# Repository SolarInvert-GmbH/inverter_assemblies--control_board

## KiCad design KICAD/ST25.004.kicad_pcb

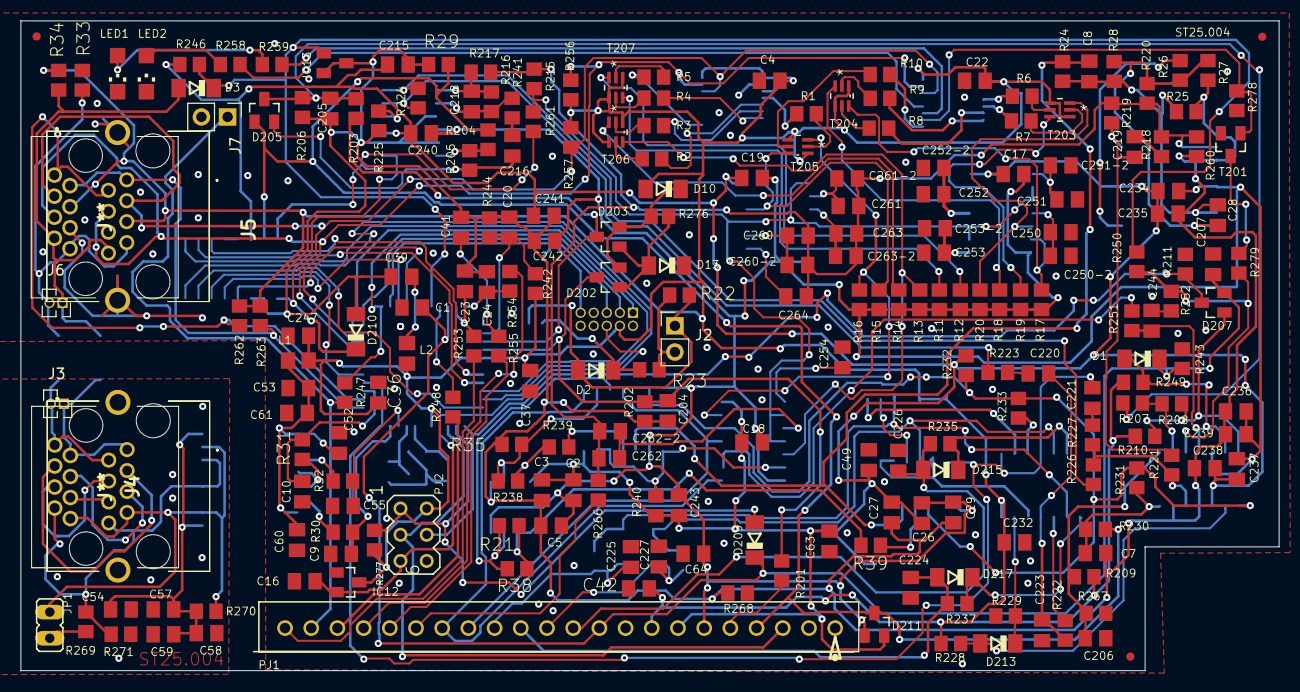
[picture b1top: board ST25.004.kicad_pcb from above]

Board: 2 copper layers, 122.0 x 63.0 mm, 257 parts (0 on the bottom side), 169 nets.

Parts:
C1, C52, C205, C207, C244, C252: 10nF; C0805K
C2, C3, C4, C5, C17, C18, C19, C20, C22, C23, C24, C26, C27, C29, C37, C39, C41, C49, C54, C57, C58, C60, C61, C63, C64, C206, C215, C232, C234, C235, C236, C237, C238, C239, C240, C241, C242, C243, C247: 100nF; C0805K
C7, C224, C225, C226, C227: 100pF; C0805K
C8, C28: n.b.; C0805K
C9, C10, C55, C245, C246: 12pF; C0805K
C16, C36, C204, C219, C223, C250-2: 1nF; C0805K
C42, C53, C59, C216, C220, C221: 10uF/16V; C0805K
C218: 1uF; C0805K
C250, C251-2, C261: 4n7; C0805K
C251, C262-2: 5n6; C0805K
C252-2: 10n; C0805K
C253: 22nF; C0805K
C253-2: 18nF; C0805K
C254, C264: 6n8; C0805K
C260, C261-2: 3n3; C0805K
C260-2: 1n; C0805K
C262: 8n2; C0805K
C263: 15n; C0805K
C263-2: 12n; C0805K
D1, D3: BAT46; SOD80C
D2, D10, D13, D209, D210, D213, D214, D215, D216, D217: LL4148; SOD80C
D202, D203, D207, D211: BAV99; SOT23
D205: BAV70; SOT23
IC1, IC2: PCA8574PW,118; SOP65P640X110-16N
IC3, IC4, IC5, IC6, IC210: HEF4066BT; SO14
IC12: MAX809TTRG; SOT-23
IC13: LM4040BIM3-5.0; SOT-23
IC14: ADM2587EBRWZ; SO20W
IC15: ATMEGA644PA-AU; TQFP44
IC16: LM258; SOIC-8_3.9x4.9mm_P1.27mm
IC17: FODM217D; SOP-4_4.4x2.6mm_P1.27mm
IC201: LM248D; SO14
IC202: LM2901D; SO14
IC207: OP-200GS; SO16DW
IC208: HCF40106MO13TR; SO14
IC209: HEF4093BT; SO14
IC211: MX7524LCSE; SO16
J1: n.b.; PinSocket_2x05_P1.27mm_Vertical
J2, J7: n.b.; PinHeader_1x02_P2.54mm_Vertical
J3: n.b. 1.27; PinSocket_1x02_P1.27mm_Vertical
J4, J5: RJHSE5380; RJHSE5380-SS603000-11o79merge
J6: n.b. 1.27mm; PinSocket_1x02_P1.27mm_Vertical
JP1: JP1E; JP1
L1, L2: 1k5@100MHz; 0805_0603
LED1: vlms30j1l2-gs08; CHIPLED_1206
LED2: vlmc3100-gs08; CHIPLED_1206
PJ1: SIMM22
PJ2: unbest.; CON_PJ2_AVR
PM1, PM2, PM3, PM4, PM5, PM6: TPSTP08; TP08R
Q1: C3E-20.000-12-3030-X; CRYSTALABM
R1, R2, R3, R4, R5, R6, R7, R8, R9, R10, R11, R12, R13, R14, R15, R16, R17, R18, R19, R20, R206, R211, R225, R230, R250: 47k; R0805
R21, R25, R26, R27, R33, R34, R35, R38: n.b.; R0805
R22, R23, R24, R28, R246, R276: 1k; R0805
R29, R217: 2M; R0805
R30, R31, R32, R268: 0R; R0805
R36, R37: n.b.; R_2010_5025Metric
R39, R203, R207, R228, R239, R247, R248, R249, R253, R254, R255, R260, R277: 10k; R0805
R201: 100k / 0,1%; R0805
R202: 10k 0,1%; R0805
R204, R205, R209, R221, R223, R226, R229, R232, R233, R240, R266, R278: 100k; R0805
R208, R231: 10M; R0805
R210, R241, R242: 3k3; R0805
R215, R222: 68k; R0805
R216, R219, R243: 1M; R0805
R218: 390k; R0805
R220, R252: 8k2; R0805
R224, R251, R267: 510k; R0805
R227: 160k; R0805
R234, R235, R236, R237, R279: 18k; R0805
R238: 15k; R0805
R244: NTC 10k; R0805
R256, R257, R258, R259, R262, R263: 4k7; R0805
R261: 33k; R0805
R269: 120R; R0805
R270, R271: 1k2; R0805
T201: BSS123; SOT23
T203, T204, T205, T206, T207: MMDT5401-7-F; SOT65P210X110-6N

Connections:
0V: C1.1, C4.2, C9.1, C10.2, C16.2, C22.2, C36.2, C37.2, C42.2, C49.2, C52.2, C53.2, C55.1, C60.2, C61.2, C63.2, C64.2, C206.1, C207.1, C223.1, C224.1, C225.1, C226.1, C227.1, C232.2, C244.1, C245.2, C246.2, C247.1, C250.2, C250-2.2, C251.2, C251-2.2, C252.2, C252-2.2, C253.2, C253-2.2, C254.2, D13.C, IC1.3, IC1.8, IC2.2, IC2.8, IC3.1, IC3.6, IC3.8, IC3.11, IC3.12, IC3.13, IC12.1, IC14.1, IC14.3, IC14.9, IC14.10, IC15.6, IC15.18, IC15.28, IC15.39, IC17.3, IC208.7, IC209.7, IC211.12, IC211.13, J1.2, J1.10, J5.6, J5.MH1, J5.MH2, J7.2, LED1.C, LED2.C, PJ1.9, PJ2.6, Q1.P$3, Q1.P$4, R33.2, R211.1, R229.1, R243.1, R252.2, R267.1, R268.1, R278.2, T201.R
+3V3: D10.C, D202.2, D203.2, R276.2
+5V: C4.1, C22.1, C36.1, C37.1, C42.1, C232.1, C247.2, D10.A, IC1.1, IC1.2, IC1.16, IC2.1, IC2.3, IC2.16, IC12.3, IC15.5, IC15.17, IC15.38, IC208.14, IC209.12, IC209.13, IC209.14, J1.4, J5.5, L1.2, L2.2, PJ1.8, PJ2.2, R34.2, R209.2, R210.2, R228.2, R242.2, R249.2, R256.1, R257.1, R262.1, R263.1, R277.2, T203.1, T203.4, T204.1, T204.4, T205.1, T205.4, T206.1, T206.4, T207.1, T207.4
+7V5: C2.1, C3.1, C17.1, C18.1, C19.1, C26.1, C27.1, C49.1, C63.1, C215.1, C234.1, C235.1, C237.2, C238.1, C240.2, C241.1, C243.1, D211.2, IC3.14, IC4.14, IC5.14, IC6.14, IC16.8, IC201.4, IC202.3, IC207.13, IC210.14, IC211.14, PJ1.7, R232.2, R240.1, R246.1
-7V5: C2.2, C5.1, C17.2, C18.2, C19.2, C26.2, C29.1, C64.1, C234.2, C236.1, C237.1, C239.2, C240.1, C242.2, C243.2, D211.1, IC3.7, IC4.7, IC5.7, IC6.7, IC16.4, IC201.11, IC202.12, IC207.4, IC210.7, IC210.9, PJ1.6, R11.2, R12.2, R13.2, R14.2, R15.2, R16.2, R17.2, R18.2, R19.2, R20.2
/0V5: D13.A, D202.1, D203.1, R276.1
/!r_clock: IC5.6, IC210.8, IC210.12, IC210.13, R240.2
/AREF1: D3.C, IC13.1, IC15.29, R246.2, R250.1
/A_HVCT: PJ1.19, R254.2
/A_IBRIDGE: PJ1.22, R253.2
/A_RESERVED: PJ1.18, R255.2
/D0: IC15.40, IC211.11
/D1: IC15.41, IC211.10
/D2: IC15.42, IC211.9
/D3: IC15.43, IC211.8
/D4: IC15.44, IC211.7
/D5: IC15.16, IC211.6
/D6: IC15.25, IC211.5
/D7: IC15.26, IC211.4
/DC+: PJ1.5, R201.1
/DE: C10.1, IC15.14, R31.1
/FBOFF: D207.3, IC15.1, PJ2.4, R211.2
/IMON: PJ1.17, R266.2
/IND0: IC6.12, R15.1, T205.6
/IND1: IC6.13, R14.1, T206.3
/IND2: IC5.5, R13.1, T206.6
/IND3: IC6.5, R12.1, T207.3
/IND4: IC6.6, R11.1, T207.6
/KAP0: IC4.5, R20.1, T203.3
/KAP1: IC4.13, R19.1, T203.6
/KAP2: IC4.12, R18.1, T204.3
/KAP3: IC4.6, R17.1, T204.6
/KAP4: IC5.13, R16.1, T205.3
/LED2: J7.1, PJ1.21, R247.1
/LO_THR: IC1.10, R278.1, T201.L
/OFFSD: D209.A, IC15.2, PJ2.1, R277.1
/RDSON_M1: IC5.11, IC210.4, PJ1.15
/RDSON_M2: IC5.8, IC210.1, PJ1.16
/REL1: IC15.3, PJ1.3, PJ2.3
/REL2: PJ1.20, R248.1
/RESET: C16.1, IC12.2, IC15.4, J1.6, PJ2.5
/RXD: C55.2, IC15.9, R32.2
/SCL: IC1.14, IC2.14, IC15.19, J5.3, R257.2
/SD: C1.2, C207.2, D1.C, D207.2, D209.C, IC15.31, PJ1.10, R243.2
/SDA: IC1.15, IC2.15, IC15.20, J5.4, R256.2
/SOLL: IC201.1, IC211.16, R261.1
/T101-ANS: C226.2, D215.A, PJ1.11, R235.2
/T102-ANS: C227.2, D214.A, PJ1.12, R234.2
/T103-ANS: C224.2, D217.A, PJ1.13, R237.2
/T104-ANS: C225.2, D216.A, PJ1.14, R236.2
/TCK: IC15.21, J1.1
/TDI: IC15.24, IC17.4, J1.9
/TDO: IC15.23, J1.3, R247.2
/TEMP: C20.2, IC15.35, R242.1, R244.2
/TMS: IC15.22, J1.5
/TXD: C9.2, IC15.10, R30.1
/UN: D205.1, D211.3, IC211.15, PJ1.4, R29.2, R204.1, R230.2
/ZC: C221.2, IC15.11, IC15.15, IC208.1, IC208.4, IC209.1
/dreieck: IC202.5, R221.1, R226.1, R227.1
/j1: IC14.13, IC14.18, J4.7, JP1.1, R270.1
/j2: IC14.15, IC14.17, J4.8, R269.1, R271.2
/j3: C54.1, C57.1, C58.1, C59.1, IC14.12, IC14.19, R270.2
/p0: IC1.5, R7.1
/p2: IC1.6, R8.1
/p3: IC1.7, R9.1
/p4: IC1.9, R10.1
/p6: IC1.11, R259.1
/p7: IC1.12, R258.1
/q0: IC2.4, R1.1
/q1: IC2.5, R2.1
/q2: IC2.6, R3.1
/q3: IC2.7, R4.1
/q4: IC2.9, R5.1
/r2: IC16.6, IC210.2, R35.1, R238.1
/r_clock: IC3.5, IC5.12, IC202.1, IC210.5, IC210.6, R231.2, R232.1, R233.2
/rdson_beidepositiv: IC5.9, IC5.10, R251.1
/schiebepunkt: IC4.2, IC4.3, IC4.9, IC4.10, IC5.2, IC5.4, IC6.1, IC6.4, IC6.8, IC6.11, R215.1, R261.2
/sinus: C219.2, IC207.16, R219.1, R221.2
/summierpunkt: C260.2, C260-2.2, C261.2, C261-2.2, C262.2, C262-2.2, C263.2, C263-2.2, C264.2, IC207.1, R215.2, R217.1, R218.2, R219.2, R220.1, R260.1, R266.1
/üs_ref: IC202.10, R250.2, R252.1, R279.1
/üspg: C205.2, D205.3, R203.1, R206.1, R207.2
/üspg_ref: C206.2, IC202.8, R209.1, R267.2
/üstrom: C244.2, IC202.11, R251.2
AGND: C3.2, C5.2, C7.1, C20.1, C23.2, C24.2, C27.2, C29.2, C39.2, C41.2, C204.1, C205.1, C215.2, C235.2, C236.2, C238.2, C239.1, C241.2, C242.1, D210.A, IC13.2, IC13.3, IC16.5, IC201.3, IC201.10, IC201.12, IC202.4, IC202.6, IC207.2, IC211.2, IC211.3, R25.1, R27.1, R29.1, R35.2, R202.1, R206.2, R225.2, R244.1, R260.2, R268.2
GND2: C54.2, C57.2, C58.2, C59.2, IC14.11, IC14.14, IC14.16, IC14.20, R271.1
J6-Pin7: J5.7, J6.2, R33.1, R37.2
J6-Pin8: D3.A, J5.8, J6.1, R34.1, R36.2
unnamed: C7.2, IC202.7, R230.1, R231.1
unnamed: C8.1, IC3.3, IC210.10, R24.1
unnamed: C23.1, IC15.32, R253.1
unnamed: C24.1, IC15.33, R254.1
unnamed: C8.2, C28.1, IC207.6, R24.2, R25.2, R28.1
unnamed: C28.2, IC207.7, R26.2, R27.2, R28.2, R220.2
unnamed: C39.1, IC15.27, L2.1
unnamed: C41.1, IC15.34, R255.1
unnamed: C52.1, C53.1, C60.1, C61.1, IC14.2, IC14.8, L1.1
unnamed: C204.2, D202.3, IC15.37, R201.2, R202.2
unnamed: C216.1, R241.2
unnamed: C216.2, D205.2, IC201.14, R205.2
unnamed: C218.1, IC201.8, R216.2, R217.2
unnamed: C218.2, IC201.9, R216.1, R241.1
unnamed: C219.1, R218.1
unnamed: C220.1, C223.2, IC208.11, R222.1
unnamed: C220.2, R223.2
unnamed: C221.1, R227.2
unnamed: C245.1, IC15.7, Q1.P$2
unnamed: C246.1, IC15.8, Q1.P$1
unnamed: C250.1, C250-2.1, IC4.4
unnamed: C251.1, C251-2.1, IC4.1
unnamed: C252.1, C252-2.1, IC4.11
unnamed: C253.1, C253-2.1, IC4.8
unnamed: C254.1, IC5.1
unnamed: C260.1, C260-2.1, IC6.10
unnamed: C261.1, C261-2.1, IC6.2
unnamed: C262.1, C262-2.1, IC5.3
unnamed: C263.1, C263-2.1, IC6.3
unnamed: C264.1, IC6.9
unnamed: D1.A, IC202.13, R249.1
unnamed: D2.A, IC17.2, J2.1, R22.2
unnamed: D2.C, IC17.1, R23.2
unnamed: D203.3, IC15.36, R203.2
unnamed: D207.1, IC202.14, R208.1, R210.1
unnamed: D210.C, IC201.2, IC211.1
unnamed: D213.A, IC202.2, R228.1
unnamed: D213.C, IC208.13, R229.2
unnamed: D214.C, IC208.5, IC209.3, R234.1
unnamed: D215.C, IC208.6, R235.1
unnamed: D216.C, IC208.9, IC209.10, R236.1
unnamed: D217.C, IC208.8, R237.1
unnamed: IC1.4, R6.1
unnamed: IC3.4, R39.1
unnamed: IC14.4, R32.1
unnamed: IC14.5, IC14.6, R31.2
unnamed: IC14.7, R30.2
unnamed: IC15.12, J5.1, R263.2
unnamed: IC15.13, J5.2, R262.2
unnamed: IC15.30, R248.2
unnamed: IC16.1, IC16.2, R21.1, R38.1, R39.2
unnamed: IC16.3, IC210.3, R21.2, R38.2
unnamed: IC16.7, R238.2, R239.2
unnamed: IC201.5, R225.1
unnamed: IC201.6, R223.1, R224.2
unnamed: IC201.7, R224.1, R226.2
unnamed: IC201.13, R204.2, R205.1
unnamed: IC202.9, R207.1, R208.2
unnamed: IC207.10, R26.1
unnamed: IC208.2, IC209.8
unnamed: IC208.3, R233.1
unnamed: IC208.10, R222.2
unnamed: IC208.12, IC209.2, IC209.5, IC209.6
unnamed: IC209.4, IC209.9
unnamed: IC210.11, R239.1
unnamed: J2.2, R22.1, R23.1
unnamed: J3.1, J4.1, R36.1
unnamed: J3.2, J4.2, R37.1
unnamed: JP1.2, R269.2
unnamed: LED1.A, R259.2
unnamed: LED2.A, R258.2
unnamed: R1.2, T205.2
unnamed: R2.2, T206.5
unnamed: R3.2, T206.2
unnamed: R4.2, T207.5
unnamed: R5.2, T207.2
unnamed: R6.2, T203.5
unnamed: R7.2, T203.2
unnamed: R8.2, T204.5
unnamed: R9.2, T204.2
unnamed: R10.2, T205.5
unnamed: R279.2, T201.M

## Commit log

2023-05-11 First Upload
